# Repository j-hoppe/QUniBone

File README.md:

> [!IMPORTANT]
> **This repository has moved.**
> Active development now lives at **[QUniBone/QUniBoneClassic](https://github.com/QUniBone/QUniBoneClassic)**.
> Please update your bookmarks, remotes, and forks.

# QUniBone
This is the software for both
Linux-to-UNIBUS bridge "UniBone"
and
Linux-to-QBUS bridge "QBone"

"UniBone" connects a BeagleBone Black micro Linux system to ancient DEC UNIBUS,
"QBone" does the same for DEC QBUS.

UniBone/QBone can keep old PDP-11s running, by emulating devices and aiding in repair.

As UNIBUS and QBUS are quite similar, only one software project compiles for both devices.

In-source differentiation is done via "#define UNIBUS" or "#define QBUS".
Source files special to only one bus are marked with suffix "_u" respective "_q".

See project pages at retrocmp.com [for UniBone](http://retrocmp.com/projects/unibone/) and [for QBone](http://retrocmp.com/projects/qbone/)

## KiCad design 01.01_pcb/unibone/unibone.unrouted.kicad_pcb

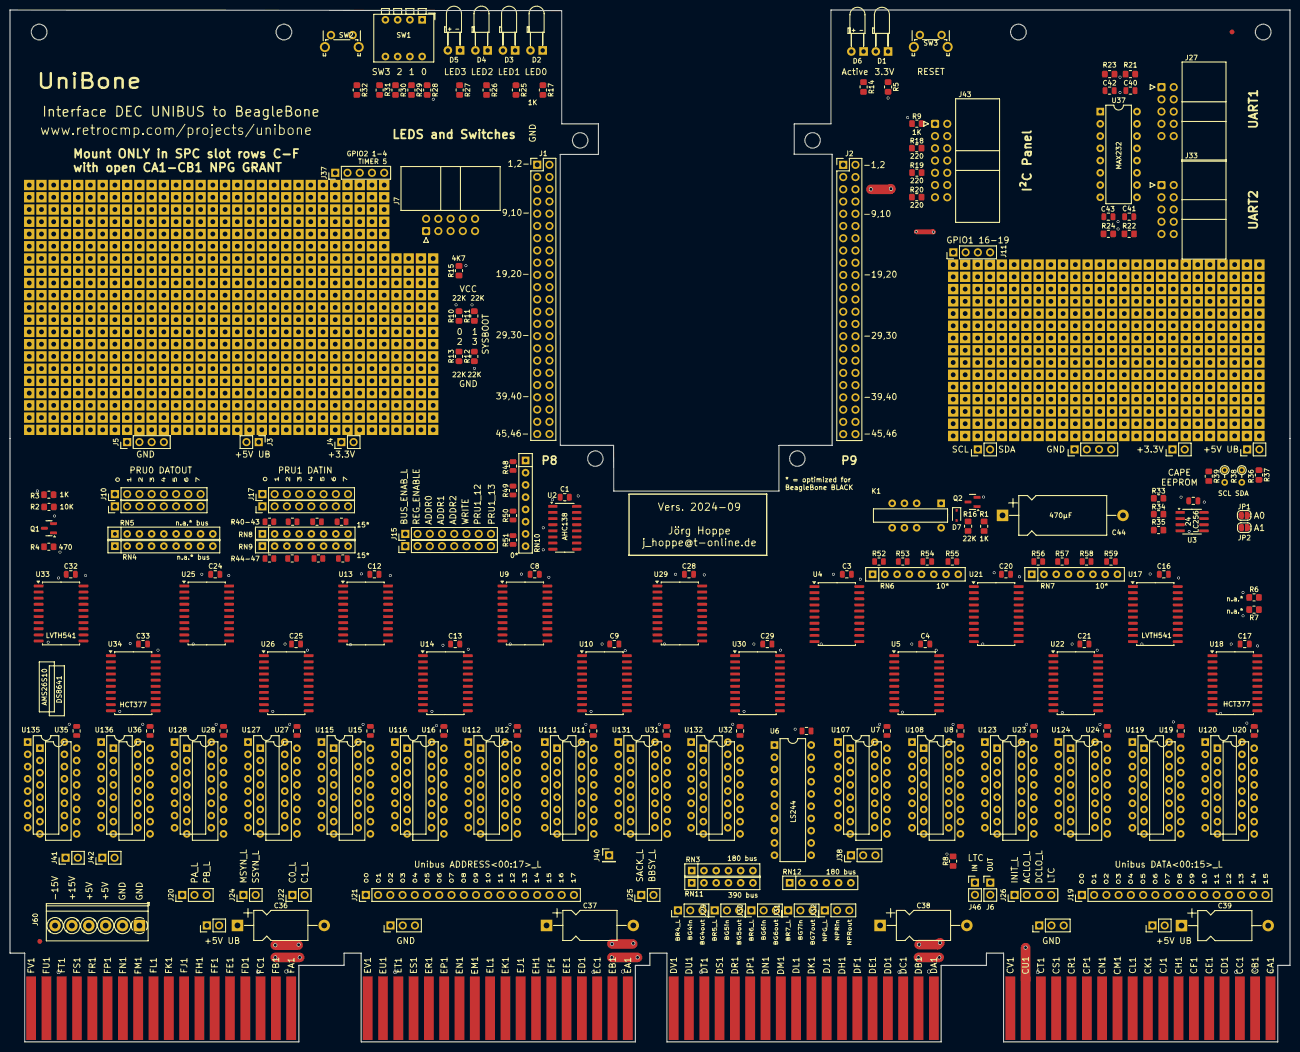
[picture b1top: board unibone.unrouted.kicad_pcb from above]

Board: 4 copper layers, 265.6 x 214.1 mm, 1317 parts (0 on the bottom side), 321 nets.

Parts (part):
C1, C2, C3, C4, C5, C6, C7, C8, C9, C10, C11, C12, C13, C14, C15, C16, C17, C18, C19, C20, C21, C22, C23, C24, C25, C26, C27, C28, C29, C30, C31, C32, C33, C34, C35: 100nF; C_0805_2012Metric
C36, C37, C38, C39: 6.3uF; CP_Axial_L11.0mm_D6.0mm_P18.00mm_Horizontal
C40, C41, C42, C43: 1uF; C_0805_2012Metric
C44: 470uF; CP_Axial_L18.0mm_D8.0mm_P25.00mm_Horizontal
D1: PWR; LED_D3.0mm_Horizontal_O3.81mm_Z2.0mm
D2: LED0; LED_D3.0mm_Horizontal_O3.81mm_Z2.0mm
D3: LED1; LED_D3.0mm_Horizontal_O3.81mm_Z2.0mm
D4: LED2; LED_D3.0mm_Horizontal_O3.81mm_Z2.0mm
D5: LED3; LED_D3.0mm_Horizontal_O3.81mm_Z2.0mm
D6: ONBUS; LED_D3.0mm_Horizontal_O3.81mm_Z2.0mm
D7: 1N4148WS; D_SOD-323
DECHANDLE1, DECHANDLE2: DEC Handle; DEC-Handle
F1, F2: Fiducial
H1, H2, H7, H8: NPTH; HOLE-3MM
HOLE1, HOLE2, HOLE3, HOLE4: MountingHole_3.2mm_M3
J1: BBB-P8; PinHeader_2x23_P2.54mm_Vertical
J2: BBB-P9; PinHeader_2x23_P2.54mm_Vertical
J3, J35: +5V UB; PinHeader_1x02_P2.54mm_Vertical
J4, J34: +3.3V; PinHeader_1x02_P2.54mm_Vertical
J5, J36: GND; PinHeader_1x04_P2.54mm_Vertical
J6: LTC_OUT; PinHeader_1x02_P2.54mm_Vertical
J7: Panel; IDC-Header_2x05_P2.54mm_Horizontal
J10: REG_DATA_FROM_PRU0; PinHeader_1x08_P2.54mm_Vertical
J11: GPIO1_16-19; PinHeader_1x04_P2.54mm_Vertical
J13, J14: GND; PinHeader_1x03_P2.54mm_Vertical
J15: PRU_CONTROL; PinHeader_1x08_P2.54mm_Vertical
J16: CONN-DEC-QUAD-CDEF; dec-conn-quad-ht-pins-only_CDEF
J17: REG_DATA_TO_PRU1; PinHeader_1x08_P2.54mm_Vertical
J19: UB_DATA; PinHeader_1x16_P2.54mm_Vertical
J20: UB_INTR_PAB; PinHeader_1x03_P2.54mm_Vertical
J21: UB_ADDR; PinHeader_1x18_P2.54mm_Vertical
J22: UB_C01; PinHeader_1x02_P2.54mm_Vertical
J23, J56, J57: GND; PinHeader_1x08_P2.54mm_Vertical
J24: UB_MSYN; PinHeader_1x02_P2.54mm_Vertical
J25: UB_SKBY; PinHeader_1x02_P2.54mm_Vertical
J26: UB_MISC; PinHeader_1x04_P2.54mm_Vertical
J27: UART1_RS232_Schneid-Klemm_2x5; IDC-Header_2x05_P2.54mm_Horizontal
J28: UB_BRG4; PinHeader_1x03_P2.54mm_Vertical
J29: UB_BRG5; PinHeader_1x03_P2.54mm_Vertical
J30: UB_BRG6; PinHeader_1x03_P2.54mm_Vertical
J31: UB_BRG7; PinHeader_1x03_P2.54mm_Vertical
J32: UB_NPRG; PinHeader_1x03_P2.54mm_Vertical
J33: UART2_RS232_Schneid-Klemm_2x5; IDC-Header_2x05_P2.54mm_Horizontal
J37: GPIO2_1-5; PinHeader_1x05_P2.54mm_Vertical
J38: -; PinHeader_1x03_P2.54mm_Vertical
J40: Conn_01x01; PinHeader_1x01_P2.54mm_Vertical
J41, J42, J61, J62: Conn_01x02_Male; PinHeader_1x02_P2.54mm_Vertical
J43: Panel_I2C; IDC-Header_2x07_P2.54mm_Horizontal
J46: LTC_IN; PinHeader_1x02_P2.54mm_Vertical
J59: I2C2; PinHeader_1x02_P2.54mm_Vertical
J60: Reichelt AKL 059-6; TerminalBlock_Phoenix_PT-1,5-6-3.5-H_1x06_P3.50mm_Horizontal
JP1: A0; SolderJumper-2_P1.3mm_Open_RoundedPad1.0x1.5mm
JP2: A1; SolderJumper-2_P1.3mm_Open_RoundedPad1.0x1.5mm
K1: HFD3; HFD3-relay
Q1, Q2: MMBT3904; SOT-23
R1, R3, R8, R9, R17, R25, R26, R27, R28, R29, R30, R31, R32: 1K; R_0805_2012Metric_Pad1.20x1.40mm_HandSolder
R2, R33, R34, R35, R37, R39: 10K; R_0805_2012Metric_Pad1.20x1.40mm_HandSolder
R4, R5, R14: 470; R_0805_2012Metric_Pad1.20x1.40mm_HandSolder
R6, R7: none; R_0805_2012Metric_Pad1.20x1.40mm_HandSolder
R10, R11, R12, R13, R16: 22K; R_0805_2012Metric_Pad1.20x1.40mm_HandSolder
R15: 4K7; R_0805_2012Metric_Pad1.20x1.40mm_HandSolder
R18, R19, R20: 220; R_0805_2012Metric_Pad1.20x1.40mm_HandSolder
R21, R22: 2K2; R_0805_2012Metric_Pad1.20x1.40mm_HandSolder
R23, R24: 3K3; R_0805_2012Metric_Pad1.20x1.40mm_HandSolder
R36, R38: opt.; R_Axial_DIN0204_L3.6mm_D1.6mm_P2.54mm_Vertical
R40, R41, R42, R43, R44, R45, R46, R47: 15; R_0805_2012Metric
R48, R49, R50, R51: 0; R_0805_2012Metric
R52, R53, R54, R55, R56, R57, R58, R59: 10; R_0805_2012Metric
RN3, RN12: 180; R_Array_SIP6
RN4, RN5: n.a.; R_Array_SIP9
RN6, RN7: 10; R_Array_SIP8
RN8, RN9: 15; R_Array_SIP8
RN10: 0; R_Array_SIP8
RN11: 390; R_Array_SIP6
SW1: SW0-3; SW_DIP_SPSTx04_Piano_CTS_Series194-4MSTN_W7.62mm_P2.54mm
SW2, SW3: BTN; SW_Tactile_SPST_Angled_PTS645Vx58-2LFS
U2: 74AHC138; SOIC-16_3.9x9.9mm_P1.27mm
U3: 24LC256; SOIC-8_3.9x4.9mm_P1.27mm
U4, U9, U13, U17, U21, U25, U29, U33: 74LVTH541_PWR; SOIC-20W_7.5x12.8mm_P1.27mm
U5, U10, U14, U18, U22, U26, U30, U34: 74HCT377; SOIC-20W_7.5x12.8mm_P1.27mm
U6: 74LS244_5V; DIP-20_W7.62mm
U7, U8, U11, U12, U15, U16, U19, U20, U23, U24, U27, U28, U31, U32, U35, U36: DS8641-LR; DIP-16_W7.62mm
U37: MAX232; DIP-16_W7.62mm
U107, U108, U111, U112, U115, U116, U119, U120, U123, U124, U127, U128, U131, U132, U135, U136: AM26S10; DIP-16_W7.62mm
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
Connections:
+3.3V: C1.2, C2.1, C3.2, C8.2, C12.2, C16.2, C20.2, C24.2, C28.2, C32.2, D1.2 (A), D2.2 (A), D3.2 (A), D4.2 (A), D5.2 (A), D6.2 (A), J2.3, J2.4, J4.1, J4.2, J34.1, J34.2, J43.5, JP1.2 (B), JP2.2 (B), R6.1, R10.1, R11.1, R35.1, R36.1, R37.1, R38.1, R39.1, RN5.1 (common), SW1.1, SW1.2, SW1.3, SW1.4, SW2.1, U2.16 (VCC), U3.8 (VCC), U4.20 (VCC), U9.20 (VCC), U13.20 (VCC), U17.20 (VCC), U21.20 (VCC), U25.20 (VCC), U29.20 (VCC), U33.20 (VCC)
+5VA: J2.5, J2.6, K1.5, K1.8, U37.16 (VCC)
/DS8641-ADR07/busdriver3/in1: U10.2 (Q0), U11.14 (in1), U111.13 (4D)
/DS8641-ADR07/busdriver3/in2: U10.5 (Q1), U11.11 (in2), U111.11 (3D)
/DS8641-ADR07/busdriver3/in3: U10.6 (Q2), U11.2 (in3), U111.4 (1D)
/DS8641-ADR07/busdriver3/in4: U10.9 (Q3), U11.5 (in4), U111.5 (2D)
/DS8641-ADR07/busdriver3/out1: U9.2 (A0), U11.13 (out1), U111.14 (4R)
/DS8641-ADR07/busdriver3/out2: U9.3 (A1), U11.10 (out2), U111.10 (3R)
/DS8641-ADR07/busdriver3/out3: U9.4 (A2), U11.3 (out3), U111.3 (1R)
/DS8641-ADR07/busdriver3/out4: U9.5 (A3), U11.6 (out4), U111.6 (2R)
/DS8641-ADR07/busdriver4/in1: U10.12 (Q4), U12.14 (in1), U112.13 (4D)
/DS8641-ADR07/busdriver4/in2: U10.15 (Q5), U12.11 (in2), U112.11 (3D)
/DS8641-ADR07/busdriver4/in3: U10.16 (Q6), U12.2 (in3), U112.4 (1D)
/DS8641-ADR07/busdriver4/in4: U10.19 (Q7), U12.5 (in4), U112.5 (2D)
/DS8641-ADR07/busdriver4/out1: U9.6 (A4), U12.13 (out1), U112.14 (4R)
/DS8641-ADR07/busdriver4/out2: U9.7 (A5), U12.10 (out2), U112.10 (3R)
/DS8641-ADR07/busdriver4/out3: U9.8 (A6), U12.3 (out3), U112.3 (1R)
/DS8641-ADR07/busdriver4/out4: U9.9 (A7), U12.6 (out4), U112.6 (2R)
/DS8641-ADR167+MSYN/busdriver3/in1: U26.2 (Q0), U27.14 (in1), U127.13 (4D)
/DS8641-ADR167+MSYN/busdriver3/in2: U26.5 (Q1), U27.11 (in2), U127.11 (3D)
/DS8641-ADR167+MSYN/busdriver3/in3: U26.6 (Q2), U27.2 (in3), U127.4 (1D)
/DS8641-ADR167+MSYN/busdriver3/in4: U26.9 (Q3), U27.5 (in4), U127.5 (2D)
/DS8641-ADR167+MSYN/busdriver3/out1: U25.2 (A0), U27.13 (out1), U127.14 (4R)
/DS8641-ADR167+MSYN/busdriver3/out2: U25.3 (A1), U27.10 (out2), U127.10 (3R)
/DS8641-ADR167+MSYN/busdriver3/out3: U25.4 (A2), U27.3 (out3), U127.3 (1R)
/DS8641-ADR167+MSYN/busdriver3/out4: U25.5 (A3), U27.6 (out4), U127.6 (2R)
/DS8641-ADR167+MSYN/busdriver4/bus3: J41.1, U28.1 (bus3), U128.2 (1B)
/DS8641-ADR167+MSYN/busdriver4/bus4: J41.2, U28.4 (bus4), U128.7 (2B)
/DS8641-ADR167+MSYN/busdriver4/in1: U26.12 (Q4), U28.14 (in1), U128.13 (4D)
/DS8641-ADR167+MSYN/busdriver4/in2: U26.15 (Q5), U28.11 (in2), U128.11 (3D)
/DS8641-ADR167+MSYN/busdriver4/in3: U26.16 (Q6), U28.2 (in3), U128.4 (1D)
/DS8641-ADR167+MSYN/busdriver4/in4: U26.19 (Q7), U28.5 (in4), U128.5 (2D)
/DS8641-ADR167+MSYN/busdriver4/out1: U25.6 (A4), U28.13 (out1), U128.14 (4R)
/DS8641-ADR167+MSYN/busdriver4/out2: U25.7 (A5), U28.10 (out2), U128.10 (3R)
/DS8641-ADR167+MSYN/busdriver4/out3: U25.8 (A6), U28.3 (out3), U128.3 (1R)
/DS8641-ADR167+MSYN/busdriver4/out4: U25.9 (A7), U28.6 (out4), U128.6 (2R)
/DS8641-ADR815/busdriver3/in1: U14.2 (Q0), U15.14 (in1), U115.13 (4D)
/DS8641-ADR815/busdriver3/in2: U14.5 (Q1), U15.11 (in2), U115.11 (3D)
/DS8641-ADR815/busdriver3/in3: U14.6 (Q2), U15.2 (in3), U115.4 (1D)
/DS8641-ADR815/busdriver3/in4: U14.9 (Q3), U15.5 (in4), U115.5 (2D)
/DS8641-ADR815/busdriver3/out1: U13.2 (A0), U15.13 (out1), U115.14 (4R)
/DS8641-ADR815/busdriver3/out2: U13.3 (A1), U15.10 (out2), U115.10 (3R)
/DS8641-ADR815/busdriver3/out3: U13.4 (A2), U15.3 (out3), U115.3 (1R)
/DS8641-ADR815/busdriver3/out4: U13.5 (A3), U15.6 (out4), U115.6 (2R)
/DS8641-ADR815/busdriver4/in1: U14.12 (Q4), U16.14 (in1), U116.13 (4D)
/DS8641-ADR815/busdriver4/in2: U14.15 (Q5), U16.11 (in2), U116.11 (3D)
/DS8641-ADR815/busdriver4/in3: U14.16 (Q6), U16.2 (in3), U116.4 (1D)
/DS8641-ADR815/busdriver4/in4: U14.19 (Q7), U16.5 (in4), U116.5 (2D)
/DS8641-ADR815/busdriver4/out1: U13.6 (A4), U16.13 (out1), U116.14 (4R)
/DS8641-ADR815/busdriver4/out2: U13.7 (A5), U16.10 (out2), U116.10 (3R)
/DS8641-ADR815/busdriver4/out3: U13.8 (A6), U16.3 (out3), U116.3 (1R)
/DS8641-ADR815/busdriver4/out4: U13.9 (A7), U16.6 (out4), U116.6 (2R)
/DS8641-ARB/busdriver3/in1: U30.2 (Q0), U31.14 (in1), U131.13 (4D)
/DS8641-ARB/busdriver3/in2: U30.5 (Q1), U31.11 (in2), U131.11 (3D)
/DS8641-ARB/busdriver3/in3: U30.6 (Q2), U31.2 (in3), U131.4 (1D)
/DS8641-ARB/busdriver3/in4: U30.9 (Q3), U31.5 (in4), U131.5 (2D)
/DS8641-ARB/busdriver3/out1: U29.2 (A0), U31.13 (out1), U131.14 (4R)
/DS8641-ARB/busdriver3/out2: U29.3 (A1), U31.10 (out2), U131.10 (3R)
/DS8641-ARB/busdriver3/out3: U29.4 (A2), U31.3 (out3), U131.3 (1R)
/DS8641-ARB/busdriver3/out4: U29.5 (A3), U31.6 (out4), U131.6 (2R)
/DS8641-ARB/busdriver4/bus4: J40.1, U32.4 (bus4), U132.7 (2B)
/DS8641-ARB/busdriver4/in1: U30.12 (Q4), U32.14 (in1), U132.13 (4D)
/DS8641-ARB/busdriver4/in2: U30.15 (Q5), U32.11 (in2), U132.11 (3D)
/DS8641-ARB/busdriver4/in3: U30.16 (Q6), U32.2 (in3), U132.4 (1D)
/DS8641-ARB/busdriver4/in4: U30.19 (Q7), U32.5 (in4), U132.5 (2D)
/DS8641-ARB/busdriver4/out1: U29.6 (A4), U32.13 (out1), U132.14 (4R)
/DS8641-ARB/busdriver4/out2: U29.7 (A5), U32.10 (out2), U132.10 (3R)
/DS8641-ARB/busdriver4/out3: U29.8 (A6), U32.3 (out3), U132.3 (1R)
/DS8641-ARB/busdriver4/out4: U29.9 (A7), U32.6 (out4), U132.6 (2R)
/DS8641-DAT07/busdriver3/in1: U18.2 (Q0), U19.14 (in1), U119.13 (4D)
/DS8641-DAT07/busdriver3/in2: U18.5 (Q1), U19.11 (in2), U119.11 (3D)
/DS8641-DAT07/busdriver3/in3: U18.6 (Q2), U19.2 (in3), U119.4 (1D)
/DS8641-DAT07/busdriver3/in4: U18.9 (Q3), U19.5 (in4), U119.5 (2D)
/DS8641-DAT07/busdriver3/out1: U17.2 (A0), U19.13 (out1), U119.14 (4R)
/DS8641-DAT07/busdriver3/out2: U17.3 (A1), U19.10 (out2), U119.10 (3R)
/DS8641-DAT07/busdriver3/out3: U17.4 (A2), U19.3 (out3), U119.3 (1R)
/DS8641-DAT07/busdriver3/out4: U17.5 (A3), U19.6 (out4), U119.6 (2R)
/DS8641-DAT07/busdriver4/in1: U18.12 (Q4), U20.14 (in1), U120.13 (4D)
/DS8641-DAT07/busdriver4/in2: U18.15 (Q5), U20.11 (in2), U120.11 (3D)
/DS8641-DAT07/busdriver4/in3: U18.16 (Q6), U20.2 (in3), U120.4 (1D)
/DS8641-DAT07/busdriver4/in4: U18.19 (Q7), U20.5 (in4), U120.5 (2D)
/DS8641-DAT07/busdriver4/out1: U17.6 (A4), U20.13 (out1), U120.14 (4R)
/DS8641-DAT07/busdriver4/out2: U17.7 (A5), U20.10 (out2), U120.10 (3R)
/DS8641-DAT07/busdriver4/out3: U17.8 (A6), U20.3 (out3), U120.3 (1R)
/DS8641-DAT07/busdriver4/out4: U17.9 (A7), U20.6 (out4), U120.6 (2R)
/DS8641-DAT815/busdriver3/in1: U22.2 (Q0), U23.14 (in1), U123.13 (4D)
/DS8641-DAT815/busdriver3/in2: U22.5 (Q1), U23.11 (in2), U123.11 (3D)
/DS8641-DAT815/busdriver3/in3: U22.6 (Q2), U23.2 (in3), U123.4 (1D)
/DS8641-DAT815/busdriver3/in4: U22.9 (Q3), U23.5 (in4), U123.5 (2D)
/DS8641-DAT815/busdriver3/out1: U21.2 (A0), U23.13 (out1), U123.14 (4R)
/DS8641-DAT815/busdriver3/out2: U21.3 (A1), U23.10 (out2), U123.10 (3R)
/DS8641-DAT815/busdriver3/out3: U21.4 (A2), U23.3 (out3), U123.3 (1R)
/DS8641-DAT815/busdriver3/out4: U21.5 (A3), U23.6 (out4), U123.6 (2R)
/DS8641-DAT815/busdriver4/in1: U22.12 (Q4), U24.14 (in1), U124.13 (4D)
/DS8641-DAT815/busdriver4/in2: U22.15 (Q5), U24.11 (in2), U124.11 (3D)
/DS8641-DAT815/busdriver4/in3: U22.16 (Q6), U24.2 (in3), U124.4 (1D)
/DS8641-DAT815/busdriver4/in4: U22.19 (Q7), U24.5 (in4), U124.5 (2D)
/DS8641-DAT815/busdriver4/out1: U21.6 (A4), U24.13 (out1), U124.14 (4R)
/DS8641-DAT815/busdriver4/out2: U21.7 (A5), U24.10 (out2), U124.10 (3R)
/DS8641-DAT815/busdriver4/out3: U21.8 (A6), U24.3 (out3), U124.3 (1R)
/DS8641-DAT815/busdriver4/out4: U21.9 (A7), U24.6 (out4), U124.6 (2R)
/DS8641-SSYN+MISC/busdriver3/in1: U34.2 (Q0), U35.14 (in1), U135.13 (4D)
/DS8641-SSYN+MISC/busdriver3/in2: U34.5 (Q1), U35.11 (in2), U135.11 (3D)
/DS8641-SSYN+MISC/busdriver3/in3: U34.6 (Q2), U35.2 (in3), U135.4 (1D)
/DS8641-SSYN+MISC/busdriver3/in4: U34.9 (Q3), U35.5 (in4), U135.5 (2D)
/DS8641-SSYN+MISC/busdriver3/out1: U33.2 (A0), U35.13 (out1), U135.14 (4R)
/DS8641-SSYN+MISC/busdriver3/out2: U33.3 (A1), U35.10 (out2), U135.10 (3R)
/DS8641-SSYN+MISC/busdriver3/out3: U33.4 (A2), U35.3 (out3), U135.3 (1R)
/DS8641-SSYN+MISC/busdriver3/out4: U33.5 (A3), U35.6 (out4), U135.6 (2R)
/DS8641-SSYN+MISC/busdriver4/bus3: J42.1, U36.1 (bus3), U136.2 (1B)
/DS8641-SSYN+MISC/busdriver4/bus4: J42.2, U36.4 (bus4), U136.7 (2B)
/DS8641-SSYN+MISC/busdriver4/in1: U34.12 (Q4), U36.14 (in1), U136.13 (4D)
/DS8641-SSYN+MISC/busdriver4/in2: U34.15 (Q5), U36.11 (in2), U136.11 (3D)
/DS8641-SSYN+MISC/busdriver4/in3: U34.16 (Q6), U36.2 (in3), U136.4 (1D)
/DS8641-SSYN+MISC/busdriver4/in4: U34.19 (Q7), U36.5 (in4), U136.5 (2D)
/DS8641-SSYN+MISC/busdriver4/out1: U33.6 (A4), U36.13 (out1), U136.14 (4R)
/DS8641-SSYN+MISC/busdriver4/out2: U33.7 (A5), U36.10 (out2), U136.10 (3R)
/DS8641-SSYN+MISC/busdriver4/out3: U33.8 (A6), U36.3 (out3), U136.3 (1R)
/DS8641-SSYN+MISC/busdriver4/out4: U33.9 (A7), U36.6 (out4), U136.6 (2R)
/SELECT0_L: U2.15 (O0), U4.19 (G2), U5.1 (EO)
/SELECT1_L: U2.14 (O1), U29.19 (G2), U30.1 (EO)
/SELECT2_L: U2.13 (O2), U9.19 (G2), U10.1 (EO)
/SELECT3_L: U2.12 (O3), U13.19 (G2), U14.1 (EO)
/SELECT4_L: U2.11 (O4), U25.19 (G2), U26.1 (EO)
/SELECT5_L: U2.10 (O5), U17.19 (G2), U18.1 (EO)
/SELECT6_L: U2.9 (O6), U21.19 (G2), U22.1 (EO)
/SELECT7_L: U2.7 (O7), U33.19 (G2), U34.1 (EO)
/TTL_IN_OUT/BUS_IN_DAT6: J38.1, U6.15 (I2b)
/TTL_IN_OUT/BUS_IN_DAT7: J38.2, U6.17 (I3b)
/TTL_IN_OUT/busdriver1/in1: U5.2 (Q0), U8.14 (in1), U108.13 (4D)
/TTL_IN_OUT/busdriver1/in2: U5.5 (Q1), U8.11 (in2), U108.11 (3D)
/TTL_IN_OUT/busdriver1/in3: U5.6 (Q2), U8.2 (in3), U108.4 (1D)
/TTL_IN_OUT/busdriver1/in4: U5.9 (Q3), U8.5 (in4), U108.5 (2D)
/TTL_IN_OUT/busdriver1/out1: U8.13 (out1), U108.14 (4R)
/TTL_IN_OUT/busdriver1/out2: U8.10 (out2), U108.10 (3R)
/TTL_IN_OUT/busdriver1/out3: U8.3 (out3), U108.3 (1R)
/TTL_IN_OUT/busdriver1/out4: U8.6 (out4), U108.6 (2R)
/TTL_IN_OUT/busdriver2/bus3: J38.3, U7.1 (bus3), U107.2 (1B)
/TTL_IN_OUT/busdriver2/in1: U5.12 (Q4), U7.14 (in1), U107.13 (4D)
/TTL_IN_OUT/busdriver2/in2: U5.15 (Q5), U7.11 (in2), U107.11 (3D)
/TTL_IN_OUT/busdriver2/in3: U5.16 (Q6), U7.2 (in3), U107.4 (1D)
/TTL_IN_OUT/busdriver2/out1: U7.13 (out1), U107.14 (4R)
/TTL_IN_OUT/busdriver2/out2: U7.10 (out2), U107.10 (3R)
/TTL_IN_OUT/busdriver2/out3: U7.3 (out3), U107.3 (1R)
/TTL_IN_OUT/busdriver2/out4: U7.6 (out4), U107.6 (2R)
/misc-io/EEPROM_A0: JP1.1 (A), R33.1, U3.1 (A0)
/misc-io/EEPROM_A1: JP2.1 (A), R34.1, U3.2 (A1)
BG4_IN_H: J16.DS2, J28.2, RN3.2 (R1), RN11.2 (R1), U6.2 (I0a)
BG4_OUT_H: J16.DT2, J28.3, RN12.2 (R1), U8.15 (bus1), U108.15 (4B)
BG5_IN_H: J16.DP2, J29.2, RN3.3 (R2), RN11.3 (R2), U6.4 (I1a)
BG5_OUT_H: J16.DR2, J29.3, RN12.3 (R2), U8.12 (bus2), U108.9 (3B)
BG6_IN_H: J16.DM2, J30.2, RN3.4 (R3), RN11.4 (R3), U6.6 (I2a)
BG6_OUT_H: J16.DN2, J30.3, RN12.4 (R3), U8.1 (bus3), U108.2 (1B)
BG7_IN_H: J16.DK2, J31.2, RN3.5 (R4), RN11.5 (R4), U6.8 (I3a)
BG7_OUT_H: J16.DL2, J31.3, RN12.5 (R4), U8.4 (bus4), U108.7 (2B)
BUS_ENABLE: J1.11, R2.2, R3.2
BUS_ENABLE_L: J15.1, Q1.3 (C), R4.2, U7.9 (disA), U8.9 (disA), U11.9 (disA), U12.9 (disA), U15.9 (disA), U16.9 (disA), U19.9 (disA), U20.9 (disA), U23.9 (disA), U24.9 (disA), U27.9 (disA), U28.9 (disA), U31.9 (disA), U32.9 (disA), U35.9 (disA), U36.9 (disA), U107.12 (S), U108.12 (S), U111.12 (S), U112.12 (S), U115.12 (S), U116.12 (S), U119.12 (S), U120.12 (S), U123.12 (S), U124.12 (S), U127.12 (S), U128.12 (S), U131.12 (S), U132.12 (S), U135.12 (S), U136.12 (S)
BUTTON: J1.12, J7.10, R32.1, SW2.2
GND: C1.1, C2.2, C3.1, C4.1, C5.1, C6.1, C7.1, C8.1, C9.1, C10.1, C11.1, C12.1, C13.1, C14.1, C15.1, C16.1, C17.1, C18.1, C19.1, C20.1, C21.1, C22.1, C23.1, C24.1, C25.1, C26.1, C27.1, C28.1, C29.1, C30.1, C31.1, C32.1, C33.1, C34.1, C35.1, C36.2, C37.2, C38.2, C39.2, C42.1, C43.1, C44.2, J1.1, J1.2, J2.1, J2.2, J2.43, J2.44, J2.45, J2.46, J5.1, J5.2, J5.3, J5.4, J7.9, J13.1, J13.2, J13.3, J14.1, J14.2, J14.3, J16.CC2, J16.CT1, J16.DC2, J16.DT1, J16.EC2, J16.ET1, J16.FC2, J16.FT1, J23.1, J23.2, J23.3, J23.4, J23.5, J23.6, J23.7, J23.8, J27.9 (GND), J33.9 (GND), J36.1, J36.2, J36.3, J36.4, J43.6, J43.8, J43.10, J43.12, J43.13, J43.14, J56.1, J56.2, J56.3, J56.4, J56.5, J56.6, J56.7, J56.8, J57.1, J57.2, J57.3, J57.4, J57.5, J57.6, J57.7, J57.8, J60.1, J60.2, Q1.2 (E), Q2.2 (E), R3.1, R5.2, R7.2, R9.2, R12.2, R13.2, R15.2, R23.1, R24.1, R28.2, R29.2, R30.2, R31.2, R32.2, R33.2, R34.2, RN4.1 (common), RN11.1 (common), SW3.2, U2.4 (E1), U2.5 (E2), U2.8 (GND), U3.4 (GND), U4.1 (G1), U4.10 (GND), U5.10 (GND), U6.1 (OEa), U6.10 (GND), U6.19 (OEb), U7.7 (disB), U7.8 (GND), U8.7 (disB), U8.8 (GND), U9.1 (G1), U9.10 (GND), U10.10 (GND), U11.7 (disB), U11.8 (GND), U12.7 (disB), U12.8 (GND), U13.1 (G1), U13.10 (GND), U14.10 (GND), U15.7 (disB), U15.8 (GND), U16.7 (disB), U16.8 (GND), U17.1 (G1), U17.10 (GND), U18.10 (GND), U19.7 (disB), U19.8 (GND), U20.7 (disB), U20.8 (GND), U21.1 (G1), U21.10 (GND), U22.10 (GND), U23.7 (disB), U23.8 (GND), U24.7 (disB), U24.8 (GND), U25.1 (G1), U25.10 (GND), U26.10 (GND), U27.7 (disB), U27.8 (GND), U28.7 (disB), U28.8 (GND), U29.1 (G1), U29.10 (GND), U30.10 (GND), U31.7 (disB), U31.8 (GND), U32.7 (disB), U32.8 (GND), U33.1 (G1), U33.10 (GND), U34.10 (GND), U35.7 (disB), U35.8 (GND), U36.7 (disB), U36.8 (GND), U37.15 (GND), U107.1 (GND), U107.8 (GND), U108.1 (GND), U108.8 (GND), U111.1 (GND), U111.8 (GND), U112.1 (GND), U112.8 (GND), U115.1 (GND), U115.8 (GND), U116.1 (GND), U116.8 (GND), U119.1 (GND), U119.8 (GND), U120.1 (GND), U120.8 (GND), U123.1 (GND), U123.8 (GND), U124.1 (GND), U124.8 (GND), U127.1 (GND), U127.8 (GND), U128.1 (GND), U128.8 (GND), U131.1 (GND), U131.8 (GND), U132.1 (GND), U132.8 (GND), U135.1 (GND), U135.8 (GND), U136.1 (GND), U136.8 (GND)
GPIO1_0__32: J1.25, J7.1, R17.2
GPIO1_1__33: J1.24, J7.3, R25.2
GPIO1_2__34: J1.5, J7.5, R26.2
GPIO1_3__35: J1.6, J7.7, R27.2
GPIO1_4__36: J1.23, J7.2, R28.1, SW1.8
GPIO1_5__37: J1.22, J7.4, R29.1, SW1.7
GPIO1_6__38: J1.3, J7.6, R30.1, SW1.6
GPIO1_7__39: J1.4, J7.8, R31.1, SW1.5
GPIO1_14__46: J1.16, J15.2, R15.1, U2.6 (E3)
GPIO1_16_48: J2.15, J11.1
GPIO1_17_49: J2.23, J11.2
GPIO1_18_50: J2.14, J11.3
GPIO1_19_51: J2.16, J11.4
GPIO2_1_65: J1.18, J37.1
GPIO2_2_66: J1.7, J37.2
GPIO2_3_67: J1.8, J37.3
GPIO2_4_68: J1.10, J37.4
I2C2_SCL: J2.19, J59.1, R19.1, R38.2, R39.2, U3.6 (SCL)
I2C2_SDA: J2.20, J59.2, R18.1, R36.2, R37.2, U3.5 (SDA)
LED_BUS_ACTIVITY: J2.11, R14.2
LTC_IN: J46.1, U6.13 (I1b)
LTC_OUT: J6.1, R8.2, U7.4 (bus4), U7.12 (bus2), U107.7 (2B), U107.9 (3B)
NPG_IN_H: J16.CA1, J32.2, RN3.6 (R5), RN11.6 (R5), U6.11 (I0b)
NPG_OUT_H: J16.CB1, J32.3, RN12.6 (R5), U7.15 (bus1), U107.15 (4B)
unnamed: C44.1, R1.1, R16.1
unnamed: D1.1 (K), R5.1
unnamed: D2.1 (K), R17.1
unnamed: D3.1 (K), R25.1
unnamed: D4.1 (K), R26.1
unnamed: D5.1 (K), R27.1
unnamed: D6.1 (K), R14.1
unnamed: D7.2 (A), K1.12, Q2.3 (C)
unnamed: J27.3 (RXD), U37.13 (R1IN)
unnamed: J27.5 (TXD), U37.14 (T1OUT)
unnamed: J33.3 (RXD), U37.8 (R2IN)
unnamed: J33.5 (TXD), U37.7 (T2OUT)
unnamed: J43.7, R18.2
unnamed: J43.9, R19.2
unnamed: J43.11, R9.1, R20.2
unnamed: Q1.1 (B), R2.1
unnamed: Q2.1 (B), R1.2
unnamed: R35.2, U3.3 (A2)
unnamed: U4.2 (A0), U6.18 (O0a)
unnamed: U4.3 (A1), U6.16 (O1a)
unnamed: U4.4 (A2), U6.14 (O2a)
unnamed: U4.5 (A3), U6.12 (O3a)
unnamed: U4.6 (A4), U6.9 (O0b)
unnamed: U4.7 (A5), U6.7 (O1b)
unnamed: U4.8 (A6), U6.5 (O2b)
unnamed: U4.9 (A7), U6.3 (O3b)
unnamed: C40.1, U37.1 (C1+)
unnamed: C40.2, U37.3 (C1-)
unnamed: C41.1, U37.4 (C2+)
unnamed: C41.2, U37.5 (C2-)
unnamed: R21.1, U37.12 (R1OUT)
unnamed: R22.1, U37.9 (R2OUT)
unnamed: C42.2, U37.2 (VS+)
unnamed: C43.2, U37.6 (VS-)
PANEL_RESET_L: J2.12, R20.1
PRU0_00: J2.31, R52.1, RN6.1 (R1.1)
PRU0_01: J2.29, R53.1, RN6.3 (R2.1)
PRU0_02: J2.30, R54.1, RN6.5 (R3.1)
PRU0_03: J2.28, R55.1, RN6.7 (R4.1)
PRU0_04: J2.42, R56.1, RN7.1 (R1.1)
PRU0_05: J2.27, R57.1, RN7.3 (R2.1)
PRU0_06: J2.41, R58.1, RN7.5 (R3.1)
PRU0_07: J2.25, R59.1, RN7.7 (R4.1)
PRU1_00/SYSBOOT0: J1.45, R10.2, R40.1, RN8.1 (R1.1)
PRU1_01/SYSBOOT1: J1.46, R11.2, R41.1, RN8.3 (R2.1)
PRU1_02/SYSBOOT2: J1.43, R13.1, R42.1, RN8.5 (R3.1)
PRU1_03/SYSBOOT3: J1.44, R12.1, R43.1, RN8.7 (R4.1)
PRU1_04/SYSBOOT4: J1.41, R44.1, RN9.1 (R1.1)
PRU1_05: J1.42, R45.1, RN9.3 (R2.1)
PRU1_06: J1.39, R46.1, RN9.5 (R3.1)
PRU1_07: J1.40, R47.1, RN9.7 (R4.1)
PRU1_08: J1.27, R48.1, RN10.1 (R1.1)
PRU1_09: J1.29, R49.1, RN10.3 (R2.1)
PRU1_10: J1.28, R50.1, RN10.5 (R3.1)
PRU1_11: J1.30, R51.1, RN10.7 (R4.1)
PRU1_12: J1.21, J15.7
PRU1_13: J1.20, J15.8
REG_ADR0: J15.3, R48.2, RN10.2 (R1.2), U2.1 (A0)
REG_ADR1: J15.4, R49.2, RN10.4 (R2.2), U2.2 (A1)
REG_ADR2: J15.5, R50.2, RN10.6 (R3.2), U2.3 (A2)
REG_DATIN_0: J17.1, R40.2, RN8.2 (R1.2), U4.18 (Y0), U9.18 (Y0), U13.18 (Y0), U17.18 (Y0), U21.18 (Y0), U25.18 (Y0), U29.18 (Y0), U33.18 (Y0)
REG_DATIN_1: J17.2, R41.2, RN8.4 (R2.2), U4.17 (Y1), U9.17 (Y1), U13.17 (Y1), U17.17 (Y1), U21.17 (Y1), U25.17 (Y1), U29.17 (Y1), U33.17 (Y1)
REG_DATIN_2: J17.3, R42.2, RN8.6 (R3.2), U4.16 (Y2), U9.16 (Y2), U13.16 (Y2), U17.16 (Y2), U21.16 (Y2), U25.16 (Y2), U29.16 (Y2), U33.16 (Y2)
REG_DATIN_3: J17.4, R43.2, RN8.8 (R4.2), U4.15 (Y3), U9.15 (Y3), U13.15 (Y3), U17.15 (Y3), U21.15 (Y3), U25.15 (Y3), U29.15 (Y3), U33.15 (Y3)
REG_DATIN_4: J17.5, R44.2, RN9.2 (R1.2), U4.14 (Y4), U9.14 (Y4), U13.14 (Y4), U17.14 (Y4), U21.14 (Y4), U25.14 (Y4), U29.14 (Y4), U33.14 (Y4)
REG_DATIN_5: J17.6, R45.2, RN9.4 (R2.2), U4.13 (Y5), U9.13 (Y5), U13.13 (Y5), U17.13 (Y5), U21.13 (Y5), U25.13 (Y5), U29.13 (Y5), U33.13 (Y5)
REG_DATIN_6: J17.7, R46.2, RN9.6 (R3.2), U4.12 (Y6), U9.12 (Y6), U13.12 (Y6), U17.12 (Y6), U21.12 (Y6), U25.12 (Y6), U29.12 (Y6), U33.12 (Y6)
REG_DATIN_7: J17.8, R47.2, RN9.8 (R4.2), U4.11 (Y7), U9.11 (Y7), U13.11 (Y7), U17.11 (Y7), U21.11 (Y7), U25.11 (Y7), U29.11 (Y7), U33.11 (Y7)
REG_DATOUT_0: J10.1, R52.2, RN4.2 (R1), RN5.2 (R1), RN6.2 (R1.2), U5.3 (D0), U10.3 (D0), U14.3 (D0), U18.3 (D0), U22.3 (D0), U26.3 (D0), U30.3 (D0), U34.3 (D0)
REG_DATOUT_1: J10.2, R53.2, RN4.3 (R2), RN5.3 (R2), RN6.4 (R2.2), U5.4 (D1), U10.4 (D1), U14.4 (D1), U18.4 (D1), U22.4 (D1), U26.4 (D1), U30.4 (D1), U34.4 (D1)
REG_DATOUT_2: J10.3, R54.2, RN4.4 (R3), RN5.4 (R3), RN6.6 (R3.2), U5.7 (D2), U10.7 (D2), U14.7 (D2), U18.7 (D2), U22.7 (D2), U26.7 (D2), U30.7 (D2), U34.7 (D2)
REG_DATOUT_3: J10.4, R55.2, RN4.5 (R4), RN5.5 (R4), RN6.8 (R4.2), U5.8 (D3), U10.8 (D3), U14.8 (D3), U18.8 (D3), U22.8 (D3), U26.8 (D3), U30.8 (D3), U34.8 (D3)
REG_DATOUT_4: J10.5, R56.2, RN4.6 (R5), RN5.6 (R5), RN7.2 (R1.2), U5.13 (D4), U10.13 (D4), U14.13 (D4), U18.13 (D4), U22.13 (D4), U26.13 (D4), U30.13 (D4), U34.13 (D4)
REG_DATOUT_5: J10.6, R57.2, RN4.7 (R6), RN5.7 (R6), RN7.4 (R2.2), U5.14 (D5), U10.14 (D5), U14.14 (D5), U18.14 (D5), U22.14 (D5), U26.14 (D5), U30.14 (D5), U34.14 (D5)
REG_DATOUT_6: J10.7, R58.2, RN4.8 (R7), RN5.8 (R7), RN7.6 (R3.2), U5.17 (D6), U10.17 (D6), U14.17 (D6), U18.17 (D6), U22.17 (D6), U26.17 (D6), U30.17 (D6), U34.17 (D6)
REG_DATOUT_7: J10.8, R59.2, RN4.9 (R8), RN5.9 (R8), RN7.8 (R4.2), U5.18 (D7), U10.18 (D7), U14.18 (D7), U18.18 (D7), U22.18 (D7), U26.18 (D7), U30.18 (D7), U34.18 (D7)
REG_WRITE: J15.6, R6.2, R7.1, R51.2, RN10.8 (R4.2), U5.11 (Cp), U10.11 (Cp), U14.11 (Cp), U18.11 (Cp), U22.11 (Cp), U26.11 (Cp), U30.11 (Cp), U34.11 (Cp)
SYSRESET_L: J2.10, SW3.1
TIMER5: J1.9, J37.5, U7.5 (in4), U107.5 (2D)
UART1_RXD: J2.26, R21.2, R23.2
UART1_TXD: J2.24, U37.11 (T1IN)
UART2_RXD: J2.22, R22.2, R24.2
UART2_TXD: J2.21, U37.10 (T2IN)
UB_5V: C4.2, C5.2, C6.2, C7.2, C9.2, C10.2, C11.2, C13.2, C14.2, C15.2, C17.2, C18.2, C19.2, C21.2, C22.2, C23.2, C25.2, C26.2, C27.2, C29.2, C30.2, C31.2, C33.2, C34.2, C35.2, C36.1, C37.1, C38.1, C39.1, D7.1 (K), J3.1, J3.2, J16.CA2, J16.DA2, J16.EA2, J16.FA2, J35.1, J35.2, J43.1, J43.2, J43.3, J43.4, J60.3, J60.4, J61.1, J61.2, J62.1, J62.2, K1.1, K1.4, K1.9, R4.1, R8.1, R16.2, RN3.1 (common), RN12.1 (common), U5.20 (+5V), U6.20 (+5V), U7.16 (5V), U8.16 (5V), U10.20 (+5V), U11.16 (5V), U12.16 (5V), U14.20 (+5V), U15.16 (5V), U16.16 (5V), U18.20 (+5V), U19.16 (5V), U20.16 (5V), U22.20 (+5V), U23.16 (5V), U24.16 (5V), U26.20 (+5V), U27.16 (5V), U28.16 (5V), U30.20 (+5V), U31.16 (5V), U32.16 (5V), U34.20 (+5V), U35.16 (5V), U36.16 (5V), U107.16 (5V), U108.16 (5V), U111.16 (5V), U112.16 (5V), U115.16 (5V), U116.16 (5V), U119.16 (5V), U120.16 (5V), U123.16 (5V), U124.16 (5V), U127.16 (5V), U128.16 (5V), U131.16 (5V), U132.16 (5V), U135.16 (5V), U136.16 (5V)
UB_15V: J16.CU1, J60.5
UB_-15V: J16.CB2, J16.DB2, J16.EB2, J16.FB2, J60.6
UB_A00_L: J16.EH2, J21.1, U11.15 (bus1), U111.15 (4B)
UB_A01_L: J16.EH1, J21.2, U11.12 (bus2), U111.9 (3B)
UB_A02_L: J16.EF1, J21.3, U11.1 (bus3), U111.2 (1B)
UB_A03_L: J16.EV2, J21.4, U11.4 (bus4), U111.7 (2B)
UB_A04_L: J16.EU2, J21.5, U12.15 (bus1), U112.15 (4B)
UB_A05_L: J16.EV1, J21.6, U12.12 (bus2), U112.9 (3B)
UB_A06_L: J16.EU1, J21.7, U12.1 (bus3), U112.2 (1B)
UB_A07_L: J16.EP2, J21.8, U12.4 (bus4), U112.7 (2B)
UB_A08_L: J16.EN2, J21.9, U15.15 (bus1), U115.15 (4B)
UB_A09_L: J16.ER1, J21.10, U15.12 (bus2), U115.9 (3B)
UB_A10_L: J16.EP1, J21.11, U15.1 (bus3), U115.2 (1B)
UB_A11_L: J16.EL1, J21.12, U15.4 (bus4), U115.7 (2B)
UB_A12_L: J16.EC1, J21.13, U16.15 (bus1), U116.15 (4B)
UB_A13_L: J16.EK2, J21.14, U16.12 (bus2), U116.9 (3B)
UB_A14_L: J16.EK1, J21.15, U16.1 (bus3), U116.2 (1B)
UB_A15_L: J16.ED2, J21.16, U16.4 (bus4), U116.7 (2B)
UB_A16_L: J16.EE2, J21.17, U27.15 (bus1), U127.15 (4B)
UB_A17_L: J16.ED1, J21.18, U27.12 (bus2), U127.9 (3B)
UB_ACLO_L: J16.CV1, J26.2, U36.15 (bus1), U136.15 (4B)
UB_BBSY_L: J16.FD1, J25.2, U32.1 (bus3), U132.2 (1B)
UB_BR4_L: J16.DH2, J28.1, U31.15 (bus1), U131.15 (4B)
UB_BR5_L: J16.DF2, J29.1, U31.12 (bus2), U131.9 (3B)
UB_BR6_L: J16.DE2, J30.1, U31.1 (bus3), U131.2 (1B)
UB_BR7_L: J16.DD2, J31.1, U31.4 (bus4), U131.7 (2B)
UB_C0_L: J16.EJ2, J22.1, U27.1 (bus3), U127.2 (1B)
UB_C1_L: J16.EF2, J22.2, U27.4 (bus4), U127.7 (2B)
UB_D00_L: J16.CS2, J19.1, U19.15 (bus1), U119.15 (4B)
UB_D01_L: J16.CR2, J19.2, U19.12 (bus2), U119.9 (3B)
UB_D02_L: J16.CU2, J19.3, U19.1 (bus3), U119.2 (1B)
UB_D03_L: J16.CT2, J19.4, U19.4 (bus4), U119.7 (2B)
UB_D04_L: J16.CN2, J19.5, U20.15 (bus1), U120.15 (4B)
UB_D05_L: J16.CP2, J19.6, U20.12 (bus2), U120.9 (3B)
UB_D06_L: J16.CV2, J19.7, U20.1 (bus3), U120.2 (1B)
UB_D07_L: J16.CM2, J19.8, U20.4 (bus4), U120.7 (2B)
UB_D08_L: J16.CL2, J19.9, U23.15 (bus1), U123.15 (4B)
UB_D09_L: J16.CK2, J19.10, U23.12 (bus2), U123.9 (3B)
UB_D10_L: J16.CJ2, J19.11, U23.1 (bus3), U123.2 (1B)
UB_D11_L: J16.CH1, J19.12, U23.4 (bus4), U123.7 (2B)
UB_D12_L: J16.CH2, J19.13, U24.15 (bus1), U124.15 (4B)
UB_D13_L: J16.CF2, J19.14, U24.12 (bus2), U124.9 (3B)
UB_D14_L: J16.CE2, J19.15, U24.1 (bus3), U124.2 (1B)
UB_D15_L: J16.CD2, J19.16, U24.4 (bus4), U124.7 (2B)
UB_DCLO_L: J16.CN1, J26.3, U36.12 (bus2), U136.9 (3B)
UB_INIT_L: J16.DL1, J26.1, U35.4 (bus4), U135.7 (2B)
UB_INTR_L: J16.FM1, J20.1, U35.15 (bus1), U135.15 (4B)
UB_LTC: J6.2, J16.CD1, J26.4, J46.2
UB_MSYN_L: J16.EE1, J24.1, U28.15 (bus1), U128.15 (4B)
UB_NPR_L: J16.FJ1, J32.1, U32.15 (bus1), U132.15 (4B)
UB_PA_L: J16.CC1, J20.2, U35.12 (bus2), U135.9 (3B)
UB_PB_L: J16.CS1, J20.3, U35.1 (bus3), U135.2 (1B)
UB_SACK_L: J16.FT2, J25.1, U32.12 (bus2), U132.9 (3B)
UB_SSYN_L: J16.EJ1, J24.2, U28.12 (bus2), U128.9 (3B)

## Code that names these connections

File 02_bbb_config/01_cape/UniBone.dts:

/* UniBone - Device Tree Overlay for enabling GPIOs, PRU GPIOs and UARTs
*
* This overlay is based on the BB-PRU-01 overlay
* Written by Derek Molloy for the book "Exploring BeagleBone: Tools and
* Techniques for Building with Embedded Linux" by John Wiley & Sons, 2014
* ISBN 9781118935125. Please see the file README.md in the repository root
* directory for copyright and GNU GPLv3 license information.
*/
/dts-v1/;
/plugin/;

/ {
   compatible = "ti,beaglebone", "ti,beaglebone-black";

   part-number = "UniBone";
   version = "00A0";

   /* This overlay uses the following resources */
   exclusive-use =
   // SW[0..3] input on regular GPIO
         "P8.23", "P8.22", "P8.3", "P8.4",
         // BUTTON input on regular GPIO
         "P8.12",

         // LED[0..3] output on regular GPIO
         "P8.25", "P8.24", "P8.5", "P8.6",

         // Driver & Register output enable output on regular GPIO
         "P8.11", "P8.16",

         // PRU0 REG_DATOUT[0..7] outputs
         // "P9.31", "P9.29", "P9.30", "P9.28", "P9.42", "P9.27", "P9.41", "P9.25",
	 // P9.41 & P9.42 not "exclisive" here, used by PRU
         "P9.31", "P9.29", "P9.30", "P9.28", "P9.27", "P9.25",

         // PRU1 REG_DATIN[0..7] inputs
         "P8.45", "P8.46", "P8.43", "P8.44", "P8.41", "P8.42", "P8.39", "P8.40",

         // PRU1 REG_ADR[0..2], REG_WRITE outputs
         "P8.27", "P8.29", "P8.28", "P8.30",
         // PRU1 Debugging output r30 pin 12  // ,13
         "P8.21",  // "P8.20",


         // Assert constant level on eMMC CMD input
         "P8.20",

         "P9.26", // Pin UART1 RXD
         "P9.24", // Pin UART1 TXD
         "P9.22", // Pin UART2 RXD
         "P9.21", // Pin UART2 TXD

         "P9.11",  // GPIO0_30: QBone activity LED
         "P9.12",  // GPIO1_28: I2C panel reset

         "P8.9",    // GPIO2_5: Timer5 output

         // ip used
         "pru0", "pru1",
         "uart1", "uart2"  // UARTs necessary here?
            ;

   fragment@0 {
      target = <&am33xx_pinmux>;
      __overlay__ {

        // <pinctrl memory register as offset from 0x44e10800> <value> pairs
        // value composed as sum of (SPRU73N, 9.2.2.2.0)
        // SLEWCTRL: 0 = fast, 0x40 = slow.
        // RXACTIVE: Input buffer enable. 0 = disable, 0x20 = enable
        // PULLTYPESEL: Pad pullup/pulldown. 0 = pull down, 0x10 = pull up
        // PULLUDEN: Pad pullup/down enable. 0 = enable, 0x08 = disable
        // MUXMODE: 0..7
         gpio_pins: pinmux_gpio_pins {         // The GPIO pins
            pinctrl-single,pins = <

               0x010  0x2f // SW0 input on P8.23: gpio1_4, rx, no pull up/dn, mode=7
               0x014  0x2f // SW1 input on P8.22: gpio1_5, rx, no pull up/dn, mode=7
               0x018  0x2f // SW2 input on P8.3: gpio1_6, rx, no pull up/dn, mode=7
               0x01c  0x2f // SW3 input on P8.4: gpio1_7, rx, no pull up/dn, mode=7
               0x030  0x2f // BUTTON input on P8.12: gpio1_12, rx, no pull up/dn, mode=7

               0x000  0x07 // LED0 output on P8.25: gpio1_0, pulldown, mode=7
               0x004  0x07 // LED1 output on P8.24: gpio1_1, pulldown, mode=7
               0x008  0x07 // LED2 output on P8.05: gpio1_2, pulldown, mode=7
               0x00c  0x07 // LED3 output on P8.06: gpio1_3, pulldown, mode=7
               0x038  0x17 // REG_ENABLE output on P8.16: gpio1_14, pullup, mode=7
               0x034  0x17 // BUS_ENABLE output on P8.11: gpio1_13, pullup, mode=7

               0x084 0x07 // Force constant level on eMMC CMD pin. P8.20 output gpio1_31, pulldown, mode=7

                // UARTs
               0x180 0x30 // UART1 RXD on P9.26, receiver, pullup, mode=0=UART1
               0x184 0x10 // UART1 TXD on P9.24, xmitter, pullup, mode=0=UART1
               0x150 0x31 // UART2 RXD on P9.22, receiver, pullup, mode=1=UART2
               0x154 0x11 // UART2 TXD on P9.21, xmitter, pullup, mode=1=UART2

                // Activity LED
               0x070 0x07 // LED output on P9.11: gpio0_30, pulldown, mode=7
                // I2C panel reset
               0x078 0x17 // I2C panel reset on P9.12: gpio1_28, pullup, mode=7

                // 50/60Hz generation on timer 5
               0x09c  0x02 // Timer5 output on P8.09, pulldown, mode=2

            >;
         };

         pru_pru_pins: pinmux_pru_pru_pins {   // The PRU pin modes
            pinctrl-single,pins = <
                 0x190 0x15 // PRU0 REG_DATOUT_0 on P9.31: pr1_pru0_pru_r30_0, fast, pullup, mode=5
                 0x194 0x15 // PRU0 REG_DATOUT_1 on P9.29: pr1_pru0_pru_r30_1, fast, pullup, mode=5
                 0x198 0x15 // PRU0 REG_DATOUT_2 on P9.30: pr1_pru0_pru_r30_2, fast, pullup, mode=5
                 0x19c 0x15 // PRU0 REG_DATOUT_3 on P9.28: pr1_pru0_pru_r30_3, fast, pullup, mode=5
                 0x1a0 0x15 // PRU0 REG_DATOUT_4 on P9.42: pr1_pru0_pru_r30_4, fast, pullup, mode=5
                 0x1a4 0x15 // PRU0 REG_DATOUT_5 on P9.27: pr1_pru0_pru_r30_5, fast, pullup, mode=5
                 0x1a8 0x15 // PRU0 REG_DATOUT_6 on P9.41: pr1_pru0_pru_r30_6, fast, pullup, mode=5
                 0x1ac 0x15 // PRU0 REG_DATOUT_7 on P9.25: pr1_pru0_pru_r30_7, fast, pullup, mode=5
                 0x164 0x2f // P9.42 REG_DATOUT_4 tied to GPIO0_7: GPIO tristate! input, no pull up/dn, mode=7
                 0x1b4 0x2f // P9.41 REG_DATOUT_6 tied to GPIO0_20: GPIO tristate! input, no pull up/dn, mode=7

                 0x0a0 0x2e // PRU1 REG_DATIN_0 on P8.45: pr1_pru1_pru_r31_0, fast, rx, no pulldown, mode6
                 0x0a4 0x2e // PRU1 REG_DATIN_1 on P8.46: pr1_pru1_pru_r31_1, fast, rx, no pulldown, mode6
                 0x0a8 0x2e // PRU1 REG_DATIN_2 on P8.43: pr1_pru1_pru_r31_2, fast, rx, no pulldown, mode6
                 0x0ac 0x2e // PRU1 REG_DATIN_3 on P8.44: pr1_pru1_pru_r31_3, fast, rx, no pulldown, mode6
                 0x0b0 0x2e // PRU1 REG_DATIN_4 on P8.41: pr1_pru1_pru_r31_4, fast, rx, no pulldown, mode6
                 0x0b4 0x2e // PRU1 REG_DATIN_5 on P8.42: pr1_pru1_pru_r31_5, fast, rx, no pulldown, mode6
                 0x0b8 0x2e // PRU1 REG_DATIN_6 on P8.39: pr1_pru1_pru_r31_6, fast, rx, no pulldown, mode6
                 0x0bc 0x2e // PRU1 REG_DATIN_7 on P8.40: pr1_pru1_pru_r31_7, fast, rx, no pulldown, mode6
                 // 0x0bc 0x36 // PRU1 REG_DATIN_7 on P8.40: pr1_pru1_pru_r31_7, fast, rx, pullup, mode6
                 // 0x0bc 0x26 // PRU1 REG_DATIN_7 on P8.40: pr1_pru1_pru_r31_7, fast, rx, pulldown, mode6

                 // PRU1 REG_ADR[0..2], REG_WRITE outputs
                 0x0e0 0x05 // REG_ADR_0 on P8.27: pr1_pru1_pru_r30_8, fast, output, pulldown, mode=5
                 0x0e4 0x05 // REG_ADR_1 on P8.29: pr1_pru1_pru_r30_9, fast, output, pulldown, mode=5
                 0x0e8 0x05 // REG_ADR_2 on P8.28: pr1_pru1_pru_r30_10, fast, output, pulldown, mode=5
                 0x0ec 0x15 // REG_WRITE on P8.30: pr1_pru1_pru_r30_11, fast, output, pullup, mode=5
                 0x080 0x05 // PRU1_12 on P8.21: pr1_pru1_pru_r30_12, fast, output, pulldown, mode=5
                 // 0x084 0x05 // PRU1_13 on P8.20: pr1_pru1_pru_r30_13, fast, output, pulldown, mode=5

            >;
         };
      };
   };

   fragment@1 {         // Enable the PRUSS
      target = <&pruss>;
      __overlay__ {
         status = "okay";
         pinctrl-names = "default";
         pinctrl-0 = <&pru_pru_pins>;
      };
   };

   fragment@2 {         // Enable the GPIOs
      target = <&ocp>;
      __overlay__ {
         gpio_helper {
            compatible = "gpio-of-helper";
            status = "okay";
            pinctrl-names = "default";
            pinctrl-0 = <&gpio_pins>;
         };
      };
   };

   fragment@3{
            target = <&uart1>;
            __overlay__ {
                    status          = "okay";
            };
    };

   fragment@4{
            target = <&uart2>;
            __overlay__ {
                    status          = "okay";
            };
    };





};
